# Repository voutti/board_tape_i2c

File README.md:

Commodore 64 I2C breakout/adapter -board for cassette port.
* 5V side and 3.3V side. Ground is common on both.
* External passthrough for powering 5V devices
* Board has a place for a fuse. It is up to you to decide what kind of fuse you end up using  (100mA, for example).
  It is probably a good idea to do some current calculations before adding too many devices.
* Board has I2C pull-up resistors so, remove those from connected I2C modules (some sensor etc. modules have them some don't)

### Version 0.2:
Cassette port sense-pin now used for I2C SCL and write-pin used for SDA.
No need to touch solder jumpers. 

### Version 0.1:
Note 1: v0.1 requires that JP1 solder jumper is soldered (adds pull-up for SCLK on 5V side of the board).

Note 2: Board assumes that in the SW driver - cassette port SENSE line is SDA and WRITE is SCL.
        It might be better if it was the other way around since SENSE line in Commodore 64 has a
        pretty strong 3.3kOhm pull-up and any I2C slave device needs to be able to sink enough current
        to pull it low enough to be seen as logic 0. If SENSE line would be used for SCL then the strong
        pull-up would not be a problem since SCL is (usually) only controlled by I2C master. For SDA
        we could decide our own pull-up resistor value - like 4.7kOhm or 10kOhm (4.7kOhm in v0.1 board).

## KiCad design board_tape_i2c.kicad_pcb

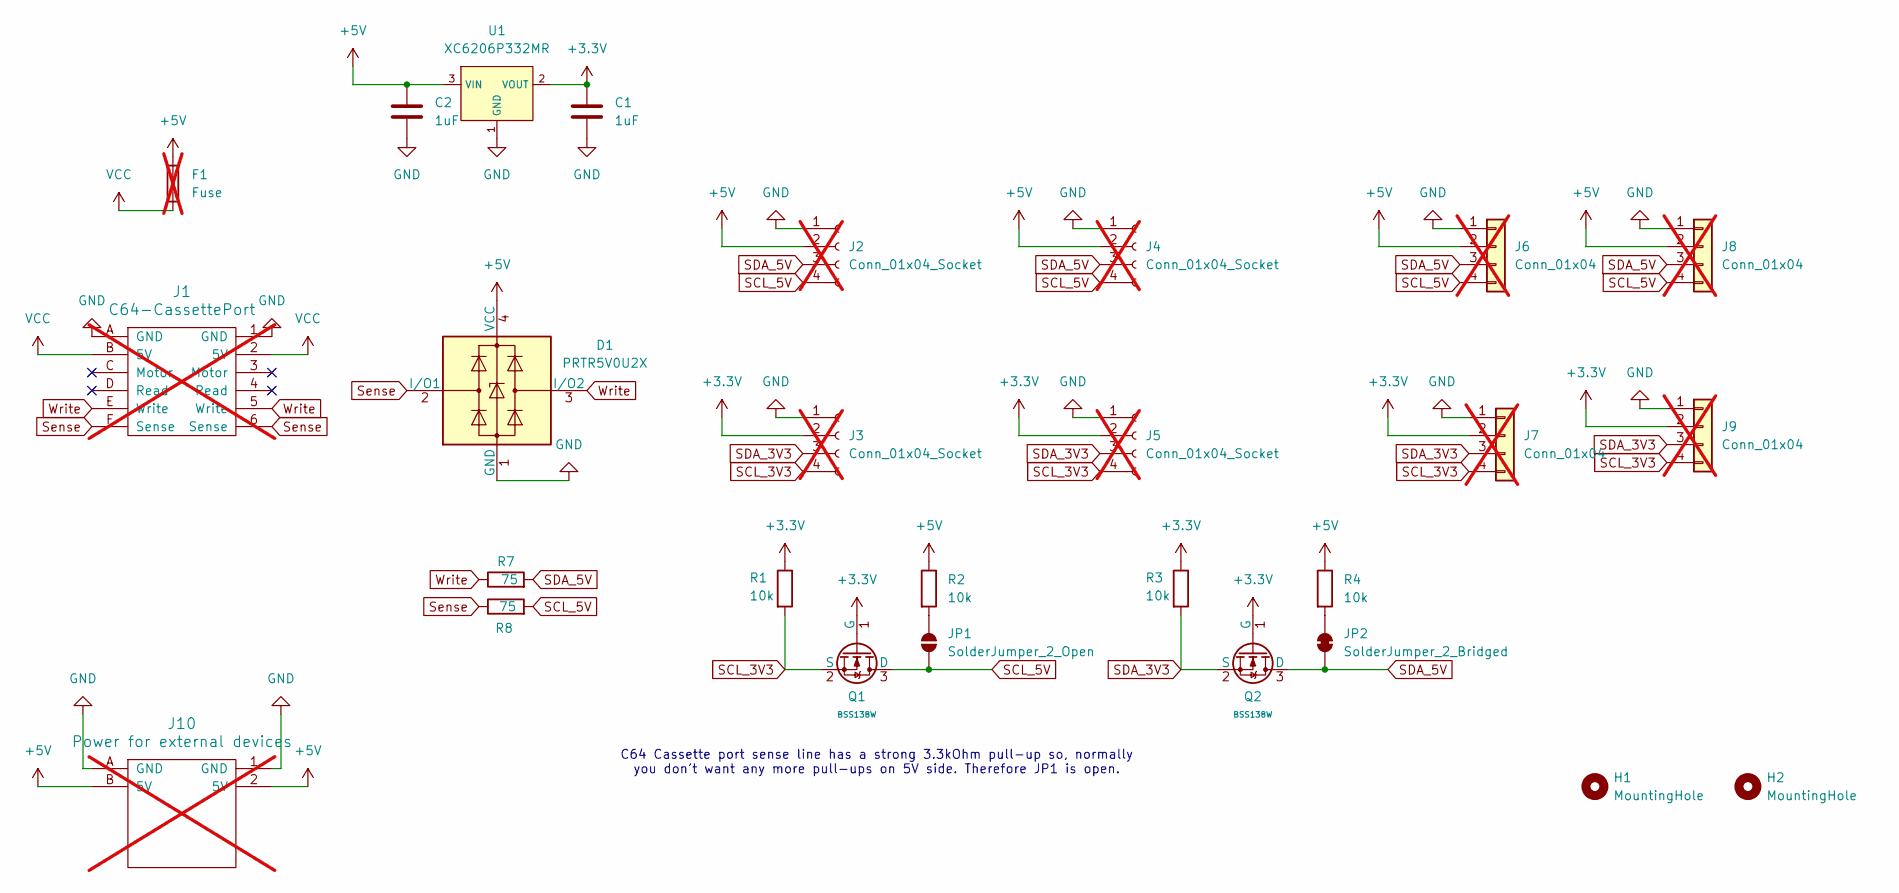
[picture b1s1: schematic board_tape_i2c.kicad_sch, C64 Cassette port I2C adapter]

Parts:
C1, C2: 1uF; C_0603
D1: PRTR5V0U2X; SOT-143
F1: Fuse; Fuseholder_Cylinder-5x20mm_Stelvio-Kontek_PTF78_Horizontal_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; not fitted
H1, H2: MountingHole; MountingHole_3.2mm_M3_Reduced
J1: C64-CassettePort; C64-Cassette-Port-Female; not fitted
J2, J3: Conn_01x04_Socket; PinHeader_1x04_P2.54mm_Vertical; not fitted
J4, J5: Conn_01x04_Socket; PinSocket_1x04_P2.54mm_Vertical; not fitted
J6, J7: Conn_01x04; JST_PH_B4B-PH-K_1x04_P2.00mm_Vertical; not fitted
J8, J9: Conn_01x04; JST_SH_BM04B-SRSS-TB_1x04-1MP_P1.00mm_Vertical; not fitted
J10: Power for external devices; C64-Cassette-Port-Male; not fitted
JP1: SolderJumper_2_Open; SolderJumper-2_P1.3mm_Open_RoundedPad1.0x1.5mm
JP2: SolderJumper_2_Bridged; SolderJumper-2_P1.3mm_Bridged2Bar_RoundedPad1.0x1.5mm
Q1, Q2: BSS138W; Q_SOT-323; Part BSS138W; LCSC C28646265
R1, R2, R3, R4: 10k; R_0603
R7, R8: 75; R_0603
U1: XC6206P332MR; SOT-23-3_L2.9-W1.6-P1.90-LS2.8-BR; Output Voltage 3.3V; Dropout Voltage 680mV@(100mA); Part XC6206P332MR-G; LCSC C5446

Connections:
+3.3V: C1.1, J3.2, J5.2, J7.2, J9.2, Q1.1 (G), Q2.1 (G), R1.1, R3.1, U1.2 (VOUT)
+5V: C2.1, D1.4 (VCC), F1.1, J2.2, J4.2, J6.2, J8.2, J10.2 (5V), J10.B (5V), R2.1, R4.1, U1.3 (VIN)
GND: C1.2, C2.2, D1.1 (GND), J1.1 (GND), J1.A (GND), J2.1, J3.1, J4.1, J5.1, J6.1, J7.1, J8.1, J9.1, J10.1 (GND), J10.A (GND), U1.1 (GND)
unnamed: JP1.2 (B), R2.2
unnamed: JP2.2 (B), R4.2
SCL_3V3: J3.4, J5.4, J7.4, J9.4, Q1.2 (S), R1.2
SCL_5V: J2.4, J4.4, J6.4, J8.4, JP1.1 (A), Q1.3 (D), R8.2
SDA_3V3: J3.3, J5.3, J7.3, J9.3, Q2.2 (S), R3.2
SDA_5V: J2.3, J4.3, J6.3, J8.3, JP2.1 (A), Q2.3 (D), R7.2
Sense: D1.2 (I/O1), J1.6 (Sense), J1.F (Sense), R8.1
VCC: F1.2, J1.2 (5V), J1.B (5V)
Write: D1.3 (I/O2), J1.5 (Write), J1.E (Write), R7.1

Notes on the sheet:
C64 Cassette port sense line has a strong 3.3kOhm pull-up so, normally you don't want any more pull-ups on 5V side. Therefore JP1 is open.

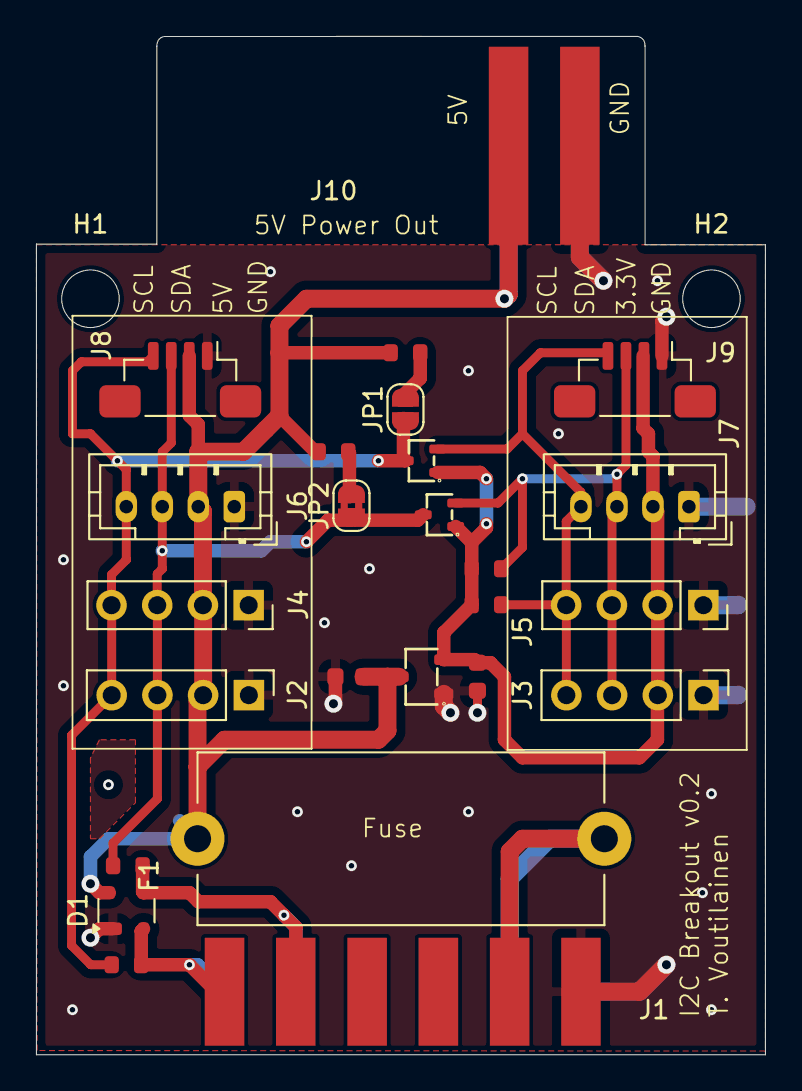
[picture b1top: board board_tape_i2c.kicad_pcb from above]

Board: 2 copper layers, 40.5 x 56.6 mm, 27 parts (0 on the bottom side), 12 nets.
